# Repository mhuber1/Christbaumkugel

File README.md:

# Christbaumkugeln_2020
 repo for Pcbways, JLCPCBs and NextPCBs Christmas givaway
 
 these PCBs schould be assembled and then hanged onto achristmas tree with U or Omega schaped piece of wire soldered into the holes on top of the right PCB
 
 for the transistors use either BC94x or BD139 not both at the same time
 C1 and C2 are supposed to be 10µF tantalum Capacitors
 R2 and R3 are 100k𝛀 resistors in a 1206 package
 the value of R1 and R4 depends on the led color used, for blue and white leds 0 ohm jumpers are recommended
 for all of the leds normal 1206 leds will work but I recommend using 1206 bottom view leds for half the amount
 for the battery holder anything like BK-912 on Digikey will work
 as a color for the soldermask i would use red or green but it doesn't really matter unless you use bottom view leds
 on on pcb there are vias on the upper part this is ment for a hook or a piece of wire that forms a loop to hang it onto a tree
 and last but not least to assemble this christmas ball slide the slots in the pcbs into each other and solder the square pads together.
 
 A proper BOM and images will come as soon as i have the pcbs at home and assembled.

just for the Giveaway: https://jlcpcb.com

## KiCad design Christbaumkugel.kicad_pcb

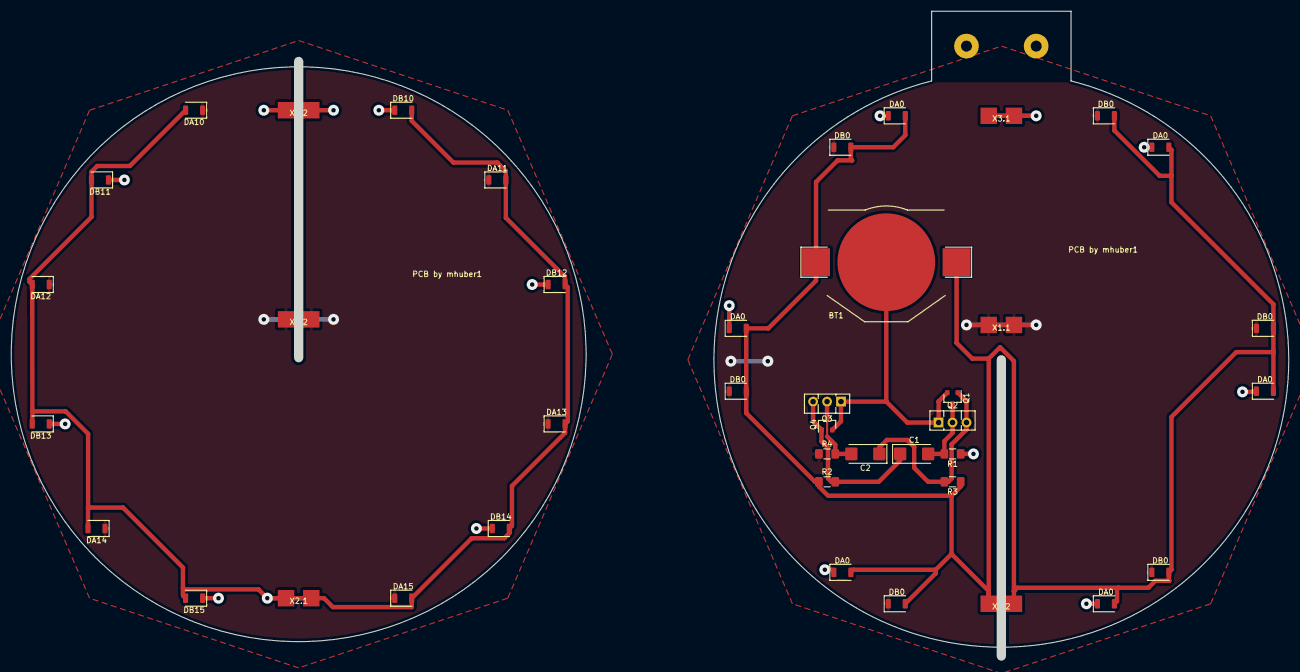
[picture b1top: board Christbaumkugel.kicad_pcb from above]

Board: 2 copper layers, 232.7 x 117.5 mm, 41 parts (0 on the bottom side), 11 nets.

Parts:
BT1: Battery_Cell; BatteryHolder_Keystone_3002_1x2032
C1, C2: 10µ; CP_EIA-6032-28_Kemet-C_Pad2.25x2.35mm_HandSolder
DA0, DA0#2, DA0#3, DA0#4, DA0#5, DA0#6, DA10, DA11, DA12, DA13, DA14, DA15: LED; LED_1206_3216Metric_ReverseMount_Hole1.8x2.4mm
DB0, DB0#2, DB0#3, DB0#4, DB0#5, DB0#6, DB10, DB11, DB12, DB13, DB14, DB15: LED; LED_1206_3216Metric_ReverseMount_Hole1.8x2.4mm
Q1, Q4: BC846; SOT-23
Q2, Q3: BD139; TO-126-3_Vertical
R1, R4: R; R_1206_3216Metric_Pad1.42x1.75mm_HandSolder
R2, R3: 100k; R_1206_3216Metric_Pad1.42x1.75mm_HandSolder
X1.1, X1.2, X2.1, X2.2, X3.1, X3.2: Pad; Pad_7.6x3

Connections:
+BATT: BT1.1, DA0.2, DA0#2.2, DA0#3.2, DA0#4.2, DA0#5.2, DA0#6.2, DB0.2, DB0#2.2, DB0#3.2, DB0#4.2, DB0#5.2, DB0#6.2, R2.1, R3.1, X2.2.1
LED_A: DA0.1, DA0#2.1, DA0#3.1, DA0#4.1, DA0#5.1, DA0#6.1, R1.1, X3.1.1
LED_B: DB0.1, DB0#2.1, DB0#3.1, DB0#4.1, DB0#5.1, DB0#6.1, R4.1, X1.1.1
unnamed: BT1.2, Q1.2, Q2.1, Q3.1, Q4.2
unnamed: C1.1, Q3.3, Q4.1, R2.2
unnamed: C1.2, Q1.3, Q2.2, R1.2
unnamed: C2.1, Q1.1, Q2.3, R3.2
unnamed: C2.2, Q3.2, Q4.3, R4.2
unnamed: DA10.1, DA11.1, DA12.1, DA13.1, DA14.1, DA15.1, X3.2.1
unnamed: DA10.2, DA11.2, DA12.2, DA13.2, DA14.2, DA15.2, DB10.2, DB11.2, DB12.2, DB13.2, DB14.2, DB15.2, X2.1.1
unnamed: DB10.1, DB11.1, DB12.1, DB13.1, DB14.1, DB15.1, X1.2.1
